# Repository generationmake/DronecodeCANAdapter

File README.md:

# DronecodeCANAdapter
Small PCB with CAN transceiver and dronecode connectors JST GH

## PCB

### Top

### Bottom

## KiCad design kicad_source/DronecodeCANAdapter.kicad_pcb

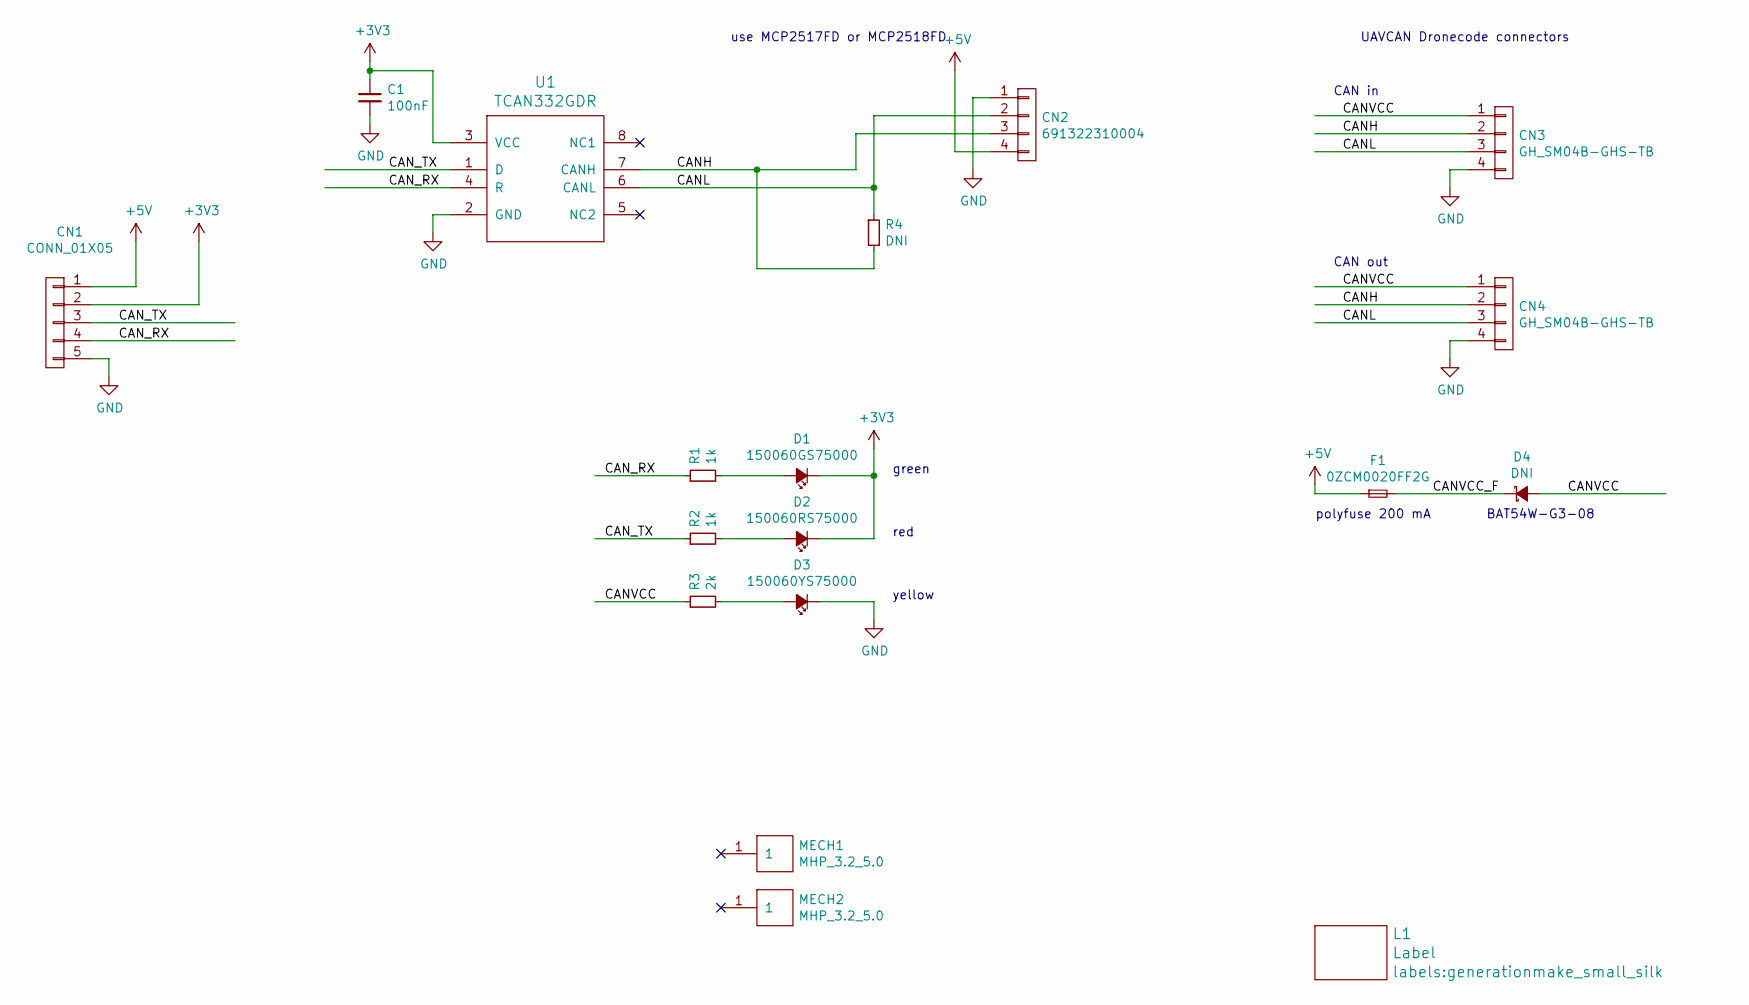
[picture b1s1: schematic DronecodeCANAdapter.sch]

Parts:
C1: 100nF; C_0603
CN1: CONN_01X05; Pin_Header_Straight_1x05
CN2: 691322310004; WR-TBL_691322310004
CN3, CN4: GH_SM04B-GHS-TB; JST_GH_SM04B-GHS-TB_1x04-1MP_P1.25mm_Horizontal
D1: 150060GS75000; LED_0603
D2: 150060RS75000; LED_0603
D3: 150060YS75000; LED_0603
D4: DNI; SOD-123
F1: 0ZCM0020FF2G; R_0603
L1: Label; generationmake_small_silk
MECH1, MECH2: MHP_3.2_5.0
R1, R2: 1k; R_0603
R3: 2k; R_0603
R4: DNI; R_0603
U1: TCAN332GDR; SOIC-8_3.9x4.9mm_Pitch1.27mm

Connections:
+3V3: C1.1, CN1.2, D1.1 (K), D2.1 (K), U1.3 (VCC)
+5V: CN1.1, CN2.4, F1.1
/CANH: CN2.3, CN3.2, CN4.2, R4.2, U1.7 (CANH)
/CANL: CN2.2, CN3.3, CN4.3, R4.1, U1.6 (CANL)
/CANVCC: CN3.1, CN4.1, D4.2 (A), R3.1
/CANVCC_F: D4.1 (K), F1.2
/CAN_RX: CN1.4, R1.1, U1.4 (R)
/CAN_TX: CN1.3, R2.1, U1.1 (D)
GND: C1.2, CN1.5, CN2.1, CN3.4, CN4.4, D3.1 (K), U1.2 (GND)
unnamed: D1.2 (A), R1.2
unnamed: D2.2 (A), R2.2
unnamed: D3.2 (A), R3.2

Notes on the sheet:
CAN in
UAVCAN Dronecode connectors
CAN out
use MCP2517FD or MCP2518FD
polyfuse 200 mA
green
red
yellow
BAT54W-G3-08

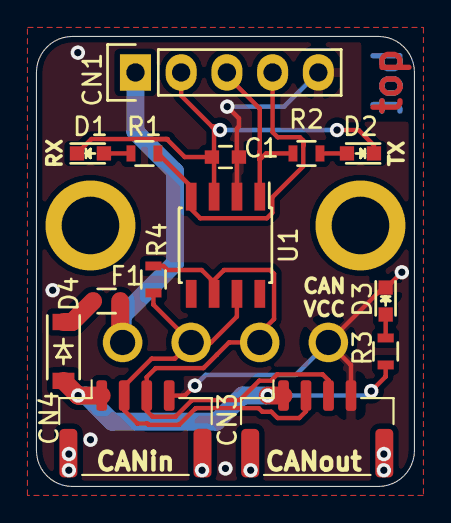
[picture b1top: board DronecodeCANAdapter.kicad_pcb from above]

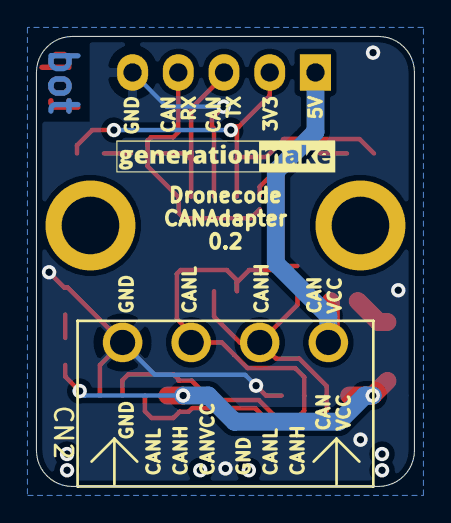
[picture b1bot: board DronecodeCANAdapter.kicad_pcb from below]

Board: 2 copper layers, 21.0 x 25.0 mm, 18 parts (2 on the bottom side), 12 nets.

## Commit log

2021-01-02 added kicad project
2021-01-02 updated schematic and layout
2021-01-02 added images and pdf schematic. updated readme
2021-01-25 corrected footprint of CAN transceiver
2021-01-25 made debug leds low active
2021-01-26 corrected polarity of leds
